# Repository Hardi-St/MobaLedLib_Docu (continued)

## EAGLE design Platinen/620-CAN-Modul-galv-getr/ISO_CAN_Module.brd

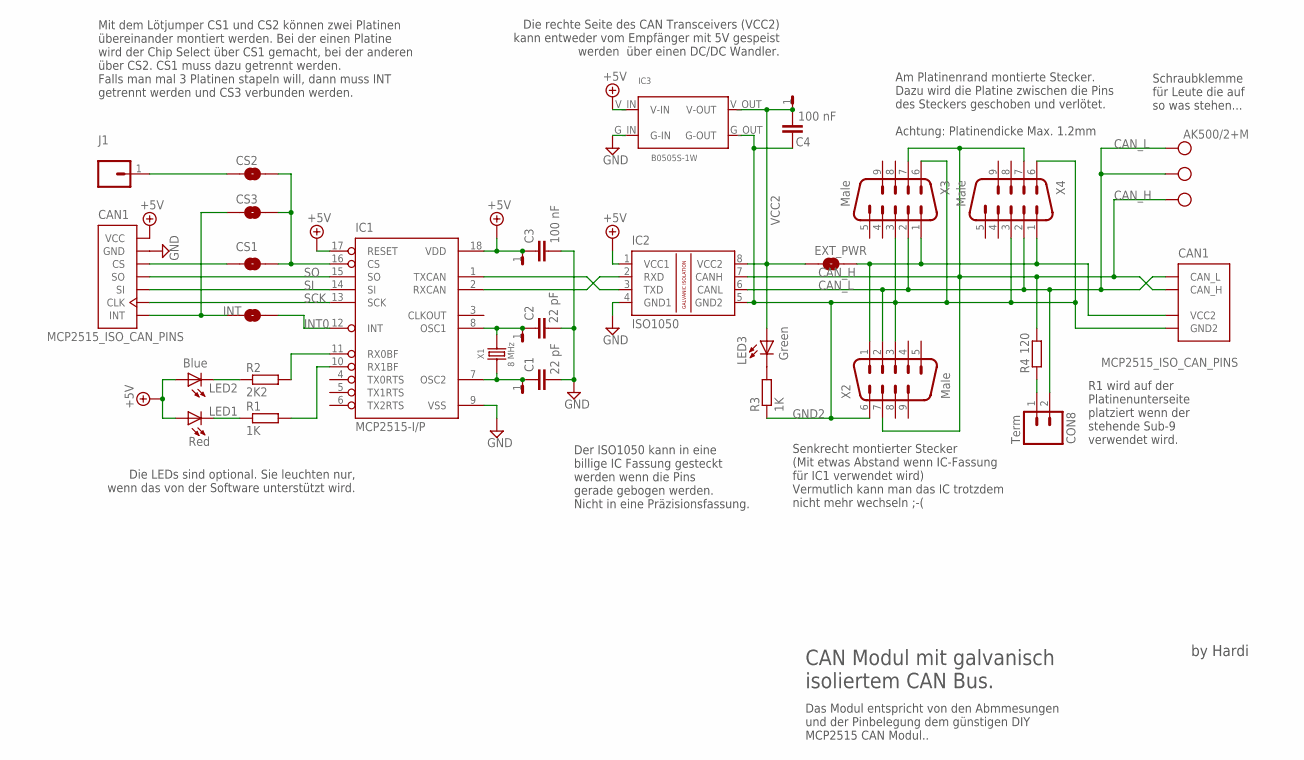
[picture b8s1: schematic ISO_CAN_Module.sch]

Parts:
C1, C2: 22 pF; C2.5-2
C3, C4: 100 nF; C2.5-2
CAN1: MCP2515_ISO_CAN_PINS; MCP2515_ISO_CAN
CON8: Term; 1X02
CS1: SOLDERJUMPERTRACE; SJ_2S-TRACE
CS2, CS3: SOLDERJUMPERNO; SJ_2S-NO
EXT_PWR: SOLDERJUMPERNO; SJ_2S-NO
IC1: MCP2515-I/P; DIL18
IC2: ISO1050; DIL08
IC3: B0505S-1W; DCDC-TEA_NME
INT: SOLDERJUMPERTRACE; SJ_2S-TRACE
J1: M01; 1X01
J2, J3, J4, J5: M01S; 1X01S
LED1: Red; CHIPLED_0805
LED2: Blue; CHIPLED_0805
LED3: Green; CHIPLED_0805
R1, R3: 1K; M0805
R2: 2K2; M0805
R4: 120; 0204/7
X1: 8 MHz; HC49U-V
X2: Male; M09VB
X3, X4: Male; M09D
X5: AK500/2+M

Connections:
+5V: C3.1, CAN1.1 (VCC), IC1.17 (RESET), IC1.18 (VDD), IC2.1 (VCC1), IC3.V_IN (V-IN), J4.1, LED1.A, LED2.A
CAN_H: CAN1.9 (CAN_H), IC2.7 (CANH), R4.2, X2.7, X3.7, X4.7, X5.2
CAN_L: CAN1.8 (CAN_L), CON8.2, IC2.6 (CANL), X2.2, X3.2, X4.2, X5.1, X5.M
CS: CS1.2, CS2.2, CS3.2, IC1.16 (CS)
CS_CAN0: CAN1.3 (CS), CS1.1
CS_INT: CAN1.7 (INT), CS3.1, INT.1
CS_J1: CS2.1, J1.1
GND: C1.2, C2.2, C3.2, CAN1.2 (GND), IC1.9 (VSS), IC2.4 (GND1), IC3.G_IN (G-IN)
GND2: C4.1, CAN1.11 (GND2), IC2.5 (GND2), IC3.G_OUT (G-OUT), R3.1, X2.3, X2.6, X3.3, X3.6, X4.3, X4.6
INT0: IC1.12 (INT), INT.2
LED1: LED1.C, R1.1
LED2: LED2.C, R2.1
LED3: LED3.C, R3.2
unnamed: IC1.11 (RX0BF), R2.2
unnamed: IC1.10 (RX1BF), R1.2
OSC1: C2.1, IC1.8 (OSC1), J3.1, X1.2
OSC2: C1.1, IC1.7 (OSC2), J2.1, X1.1
RXCAN: IC1.2 (RXCAN), IC2.2 (RXD)
SCK: CAN1.6 (CLK), IC1.13 (SCK)
SI: CAN1.5 (SI), IC1.14 (SI)
SO: CAN1.4 (SO), IC1.15 (SO)
TERM: CON8.1, R4.1
TXCAN: IC1.1 (TXCAN), IC2.3 (TXD)
VCC2: C4.2, EXT_PWR.1, IC2.8 (VCC2), IC3.V_OUT (V-OUT), J5.1, LED3.A
VCC2_EXT: CAN1.10 (VCC2), EXT_PWR.2, X2.1, X3.1, X4.1

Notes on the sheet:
Mit dem Lötjumper CS1 und CS2 können zwei Platinen übereinander montiert werden. Bei der einen Platine wird der Chip Select über CS1 gemacht, bei der anderen über CS2. CS1 muss dazu getrennt werden. Falls man mal 3 Platinen stapeln will, dann muss INT getrennt werden und CS3 verbunden werden.
Senkrecht montierter Stecker (Mit etwas Abstand wenn IC-Fassung für IC1 verwendet wird) Vermutlich kann man das IC trotzdem nicht mehr wechseln ;-(
Am Platinenrand montierte Stecker. Dazu wird die Platine zwischen die Pins des Steckers geschoben und verlötet. Achtung: Platinendicke Max. 1.2mm
Die LEDs sind optional. Sie leuchten nur, wenn das von der Software unterstützt wird.
Die rechte Seite des CAN Transceivers (VCC2) kann entweder vom Empfänger mit 5V gespeist werden über einen DC/DC Wandler.
by Hardi
CAN Modul mit galvanisch isoliertem CAN Bus.
Das Modul entspricht von den Abmmesungen und der Pinbelegung dem günstigen DIY MCP2515 CAN Modul..
Schraubklemme für Leute die auf so was stehen...
Der ISO1050 kann in eine billige IC Fassung gesteckt werden wenn die Pins gerade gebogen werden. Nicht in eine Präzisionsfassung.
R1 wird auf der Platinenunterseite platziert wenn der stehende Sub-9 verwendet wird.

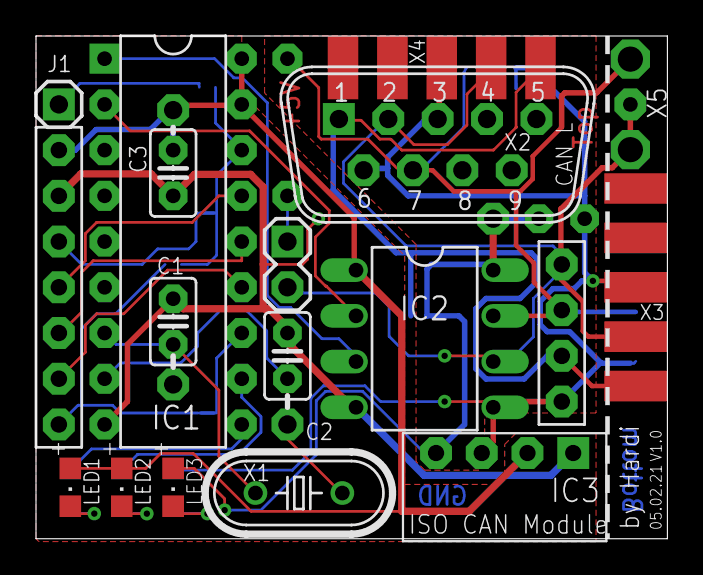
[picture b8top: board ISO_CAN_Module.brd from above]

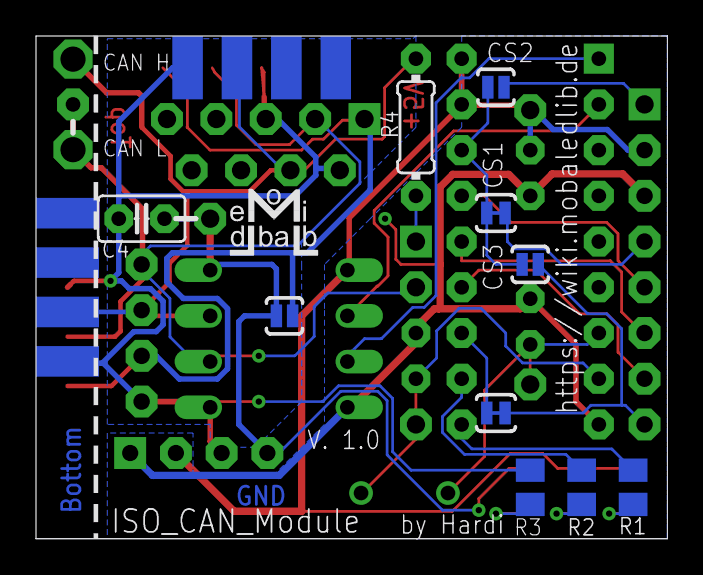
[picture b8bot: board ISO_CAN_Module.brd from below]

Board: 2 copper layers, 35.1 x 27.9 mm, 31 parts (10 on the bottom side), 25 nets.
